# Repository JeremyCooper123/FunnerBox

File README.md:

# FunnerBox

Using the FunBox guitar pedal design by GuitarML and extending/altering it to include custom rotary encoder + LED pcb modules and OLED screen.

Original FunBox Design:
https://github.com/GuitarML/FunBox.git

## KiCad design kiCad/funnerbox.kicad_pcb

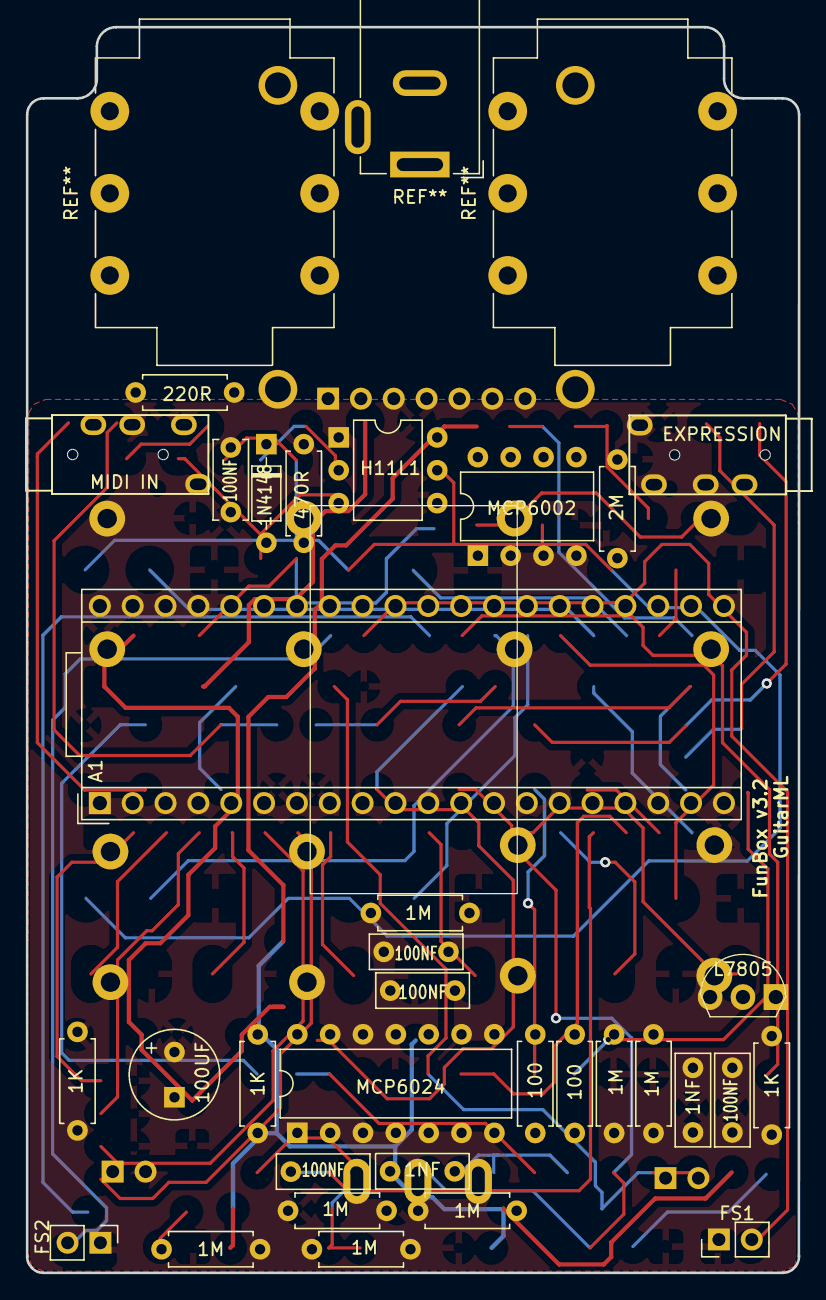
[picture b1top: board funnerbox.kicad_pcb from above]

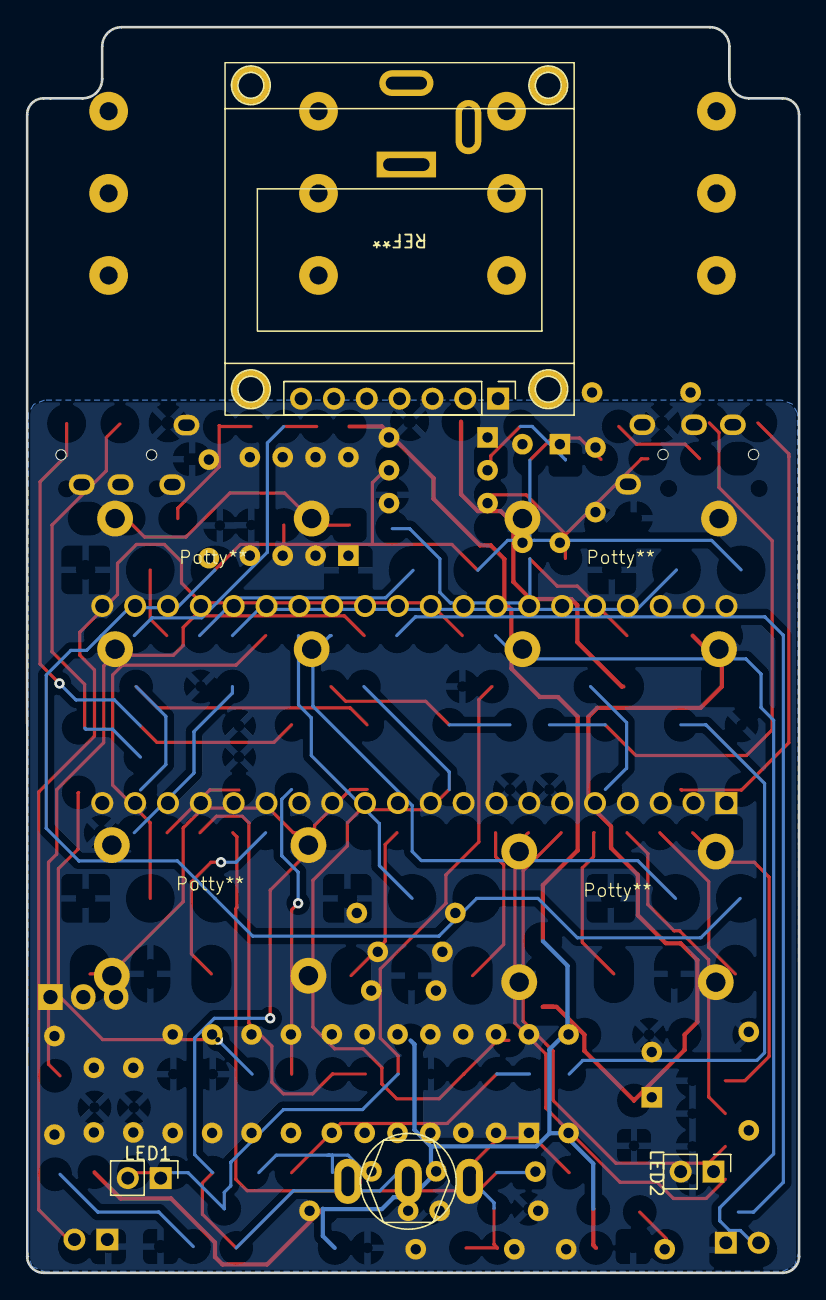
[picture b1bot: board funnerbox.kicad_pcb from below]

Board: 2 copper layers, 59.7 x 96.3 mm, 40 parts (7 on the bottom side), 27 nets.

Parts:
A1: Electrosmith_Daisy_Seed_Rev7; Electrosmith_Daisy_Seed
C3, C16: 1NF; C_Rect_L7.0mm_W2.5mm_P5.00mm
C6: 100UF; CP_Radial_D8.0mm_P3.50mm
C7, C8, C9, C10: 100NF; C_Rect_L7.0mm_W2.5mm_P5.00mm
C30: 100NF; C_Disc_D6.0mm_W2.5mm_P5.00mm
D2: 1N4148; D_DO-35_SOD27_P7.62mm_Horizontal
FS1: Foot_Switch_1; PinHeader_1x02_P2.54mm_Vertical
FS2: Foot_Switch_2; PinHeader_1x02_P2.54mm_Vertical
J6: MIDI IN; TRRS-PJ-320A
J7: EXPRESSION; TRRS-PJ-320A
LED1: LED_1; PinHeader_1x02_P2.54mm_Vertical
LED2: LED_2; PinHeader_1x02_P2.54mm_Vertical
Potty**: Potty
Potty**#2, Potty**#3, Potty**#4: Potty
R1, R2, R5, R6, R13, R15, R16: 1M; R_Axial_DIN0207_L6.3mm_D2.5mm_P7.62mm_Horizontal
R3, R8, R9: 1K; R_Axial_DIN0207_L6.3mm_D2.5mm_P7.62mm_Horizontal
R4, R17: 100; R_Axial_DIN0207_L6.3mm_D2.5mm_P7.62mm_Horizontal
R19: 2M; R_Axial_DIN0207_L6.3mm_D2.5mm_P7.62mm_Horizontal
R30: 220R; R_Axial_DIN0207_L6.3mm_D2.5mm_P7.62mm_Horizontal
R31: 470R; R_Axial_DIN0207_L6.3mm_D2.5mm_P7.62mm_Horizontal
SW2: SW_SPDT; SW_Toggle_SPDT_lugs
U1: MCP6024; DIP-14_W7.62mm
U2: L7805; TO-220-3_Vertical
U3: MCP6002; DIP-8_W7.62mm
U5: H11L1; DIP-6_W7.62mm

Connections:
3V3_A: A1.21 (3V3_A), C30.1, R31.1, U3.3 (+), U5.6
5V: C9.2, C10.2, R2.1, R5.1, R13.1, R15.1, U1.4 (V+), U2.3 (OUT), U3.8 (V+)
AUDIO_IN_BUFFER_LEFT: A1.16 (AUDIO_IN_1), U1.1, U1.2 (-)
AUDIO_IN_BUFFER_RIGHT: A1.17 (AUDIO_IN_2), U1.8, U1.9 (-)
EXPRESSION_IN: A1.22 (ADC_0), U3.6 (-), U3.7
EXPRESSION_IN_JACK: J7.T, R19.1, U3.5 (+)
EXPRESSION_REF: J7.R1, U3.1, U3.2 (-)
FOOT_SWITCH_1: A1.32 (SAI2_SD_B), FS1.2
FOOT_SWITCH_2: A1.33 (SAI2_SD_A), FS2.2
GND: A1.20 (AGND), A1.40 (DGND), C3.1, C6.1, C7.1, C8.1, C9.1, C10.1, C16.1, C30.2, FS1.1, FS2.1, J6.S, J7.S, LED1.1 (K), LED2.1 (K), R1.2, R6.2, R16.2, R19.2, SW2.2 (B), U1.11 (V-), U2.2 (GND), U3.4 (V-), U5.5
LED_1: A1.29 (DAC_OUT2), R8.2
LED_2: A1.30 (DAC_OUT1), R9.2
MIDI_IN: A1.37 (USB_D_+), R31.2, U5.4
MIDI_IN_JACK_PIN4: J6.R1, R30.1
MIDI_IN_JACK_PIN5: D2.2 (A), J6.T, U5.2
unnamed: D2.1 (K), R30.2, U5.1
unnamed: LED1.2 (A), R8.1
unnamed: LED2.2 (A), R9.1
unnamed: C3.2, R1.1, R2.2, R3.2, U1.3 (+)
unnamed: R5.2, R6.1, U1.5 (+)
unnamed: R4.1, U1.6 (-), U1.7
unnamed: C16.2, R15.2, R16.1, U1.10 (+)
unnamed: R13.2, U1.12 (+)
unnamed: R17.1, U1.13 (-), U1.14
SW2_LEFT: A1.8 (SPI1_CS), SW2.3 (C)
SW2_RIGHT: A1.11 (SPI1_PICO), SW2.1 (A)
VCC: A1.39 (VIN), C6.2, C7.2, C8.2, U2.1 (IN)

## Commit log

2026-02-02 Copied Funbox Schematic
2026-02-02 Updated Schematic to include OLED + Adding custom FPs and Symbols
2026-02-02 Updated kiCad Project
2026-02-08 Lots of stuff
2026-02-10 Added potty 3D models
